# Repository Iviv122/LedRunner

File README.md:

|Index|Quantity|Part Number          |Manufacturer Part Number|Description                     |Customer Reference|Available|Backorder|Unit Price|Extended Price PLN|
|-----|--------|---------------------|------------------------|--------------------------------|------------------|---------|---------|----------|------------------|
|1    |10      |1125-1182-ND         |MT1403-RG-A             |LED RED CLEAR 3MM ROUND T/H     |                  |10       |0        |0,62700   |6,27 zł           |
|2    |1       |296-2037-5-ND        |CD4017BE                |IC DECADE COUNTER 10BIT 16DIP   |                  |1        |0        |4,66000   |4,66 zł           |
|3    |1       |399-6596-ND          |ESK105M050AC3AA         |CAP ALUM 1UF 20% 50V RADIAL TH  |                  |1        |0        |0,55000   |0,55 zł           |
|4    |1       |399-C318C104Z5U5TA-ND|C318C104Z5U5TA          |CAP CER 0.1UF 50V Z5U RADIAL    |                  |1        |0        |0,99000   |0,99 zł           |
|5    |1       |296-NE555P-ND        |NE555P                  |IC OSC SINGLE TIMER 100KHZ 8-DIP|                  |1        |0        |1,87000   |1,87 zł           |
|6    |1       |T93YA-50K-ND         |T93YA503KT20            |TRIMMER 50K OHM 0.5W PC PIN TOP |                  |1        |0        |6,79000   |6,79 zł           |
|7    |2       |CF14JT1K00CT-ND      |CF14JT1K00              |RES 1K OHM 5% 1/4W AXIAL        |                  |2        |0        |0,37000   |0,74 zł           |
|8    |1       |738-RSMF1JT460RCT-ND |RSMF1JT460R             |RES 460 OHM 5% 1W AXIAL         |                  |1        |0        |0,51000   |0,51 zł           |

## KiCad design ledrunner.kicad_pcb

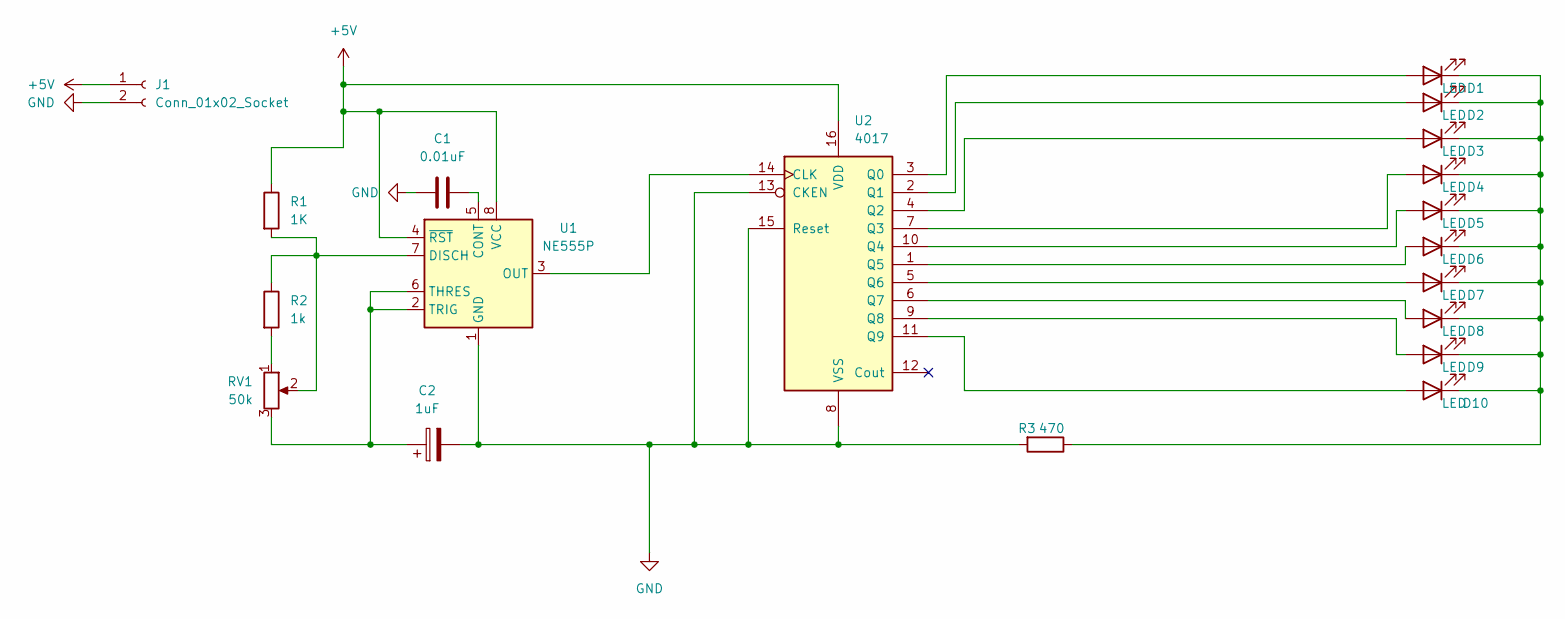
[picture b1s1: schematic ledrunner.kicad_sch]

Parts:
C1: 0.01uF; C_Disc_D7.5mm_W5.0mm_P5.00mm
C2: 1uF; CP_Radial_D5.0mm_P2.00mm
D1, D2, D3, D4, D5, D6, D7, D8, D9, D10: LED; LED_D3.0mm
J1: Conn_01x02_Socket; PinHeader_1x02_P2.54mm_Vertical
R1: 1K; R_Axial_DIN0207_L6.3mm_D2.5mm_P7.62mm_Horizontal
R2: 1k; R_Axial_DIN0207_L6.3mm_D2.5mm_P7.62mm_Horizontal
R3: 470; R_Axial_DIN0207_L6.3mm_D2.5mm_P7.62mm_Horizontal
RV1: 50k; Potentiometer_Vishay_T93YA_Vertical
U1: NE555P; DIP-8_W7.62mm
U2: 4017; N16

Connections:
+5V: J1.1, R1.1, U1.4 (~RST), U1.8 (VCC), U2.16 (VDD)
GND: C1.1, C2.2, J1.2, R3.2, U1.1 (GND), U2.8 (VSS), U2.13 (CKEN), U2.15 (Reset)
unnamed: D1.2 (A), U2.3 (Q0)
unnamed: D1.1 (K), D2.1 (K), D3.1 (K), D4.1 (K), D5.1 (K), D6.1 (K), D7.1 (K), D8.1 (K), D9.1 (K), D10.1 (K), R3.1
unnamed: D2.2 (A), U2.2 (Q1)
unnamed: D3.2 (A), U2.4 (Q2)
unnamed: D4.2 (A), U2.7 (Q3)
unnamed: D5.2 (A), U2.10 (Q4)
unnamed: D6.2 (A), U2.1 (Q5)
unnamed: D7.2 (A), U2.5 (Q6)
unnamed: D8.2 (A), U2.6 (Q7)
unnamed: D9.2 (A), U2.9 (Q8)
unnamed: D10.2 (A), U2.11 (Q9)
unnamed: R2.2, RV1.1
unnamed: C1.2, U1.5 (CONT)
unnamed: R1.2, R2.1, RV1.2, U1.7 (DISCH)
unnamed: U1.3 (OUT), U2.14 (CLK)
unnamed: C2.1, RV1.3, U1.2 (TRIG), U1.6 (THRES)

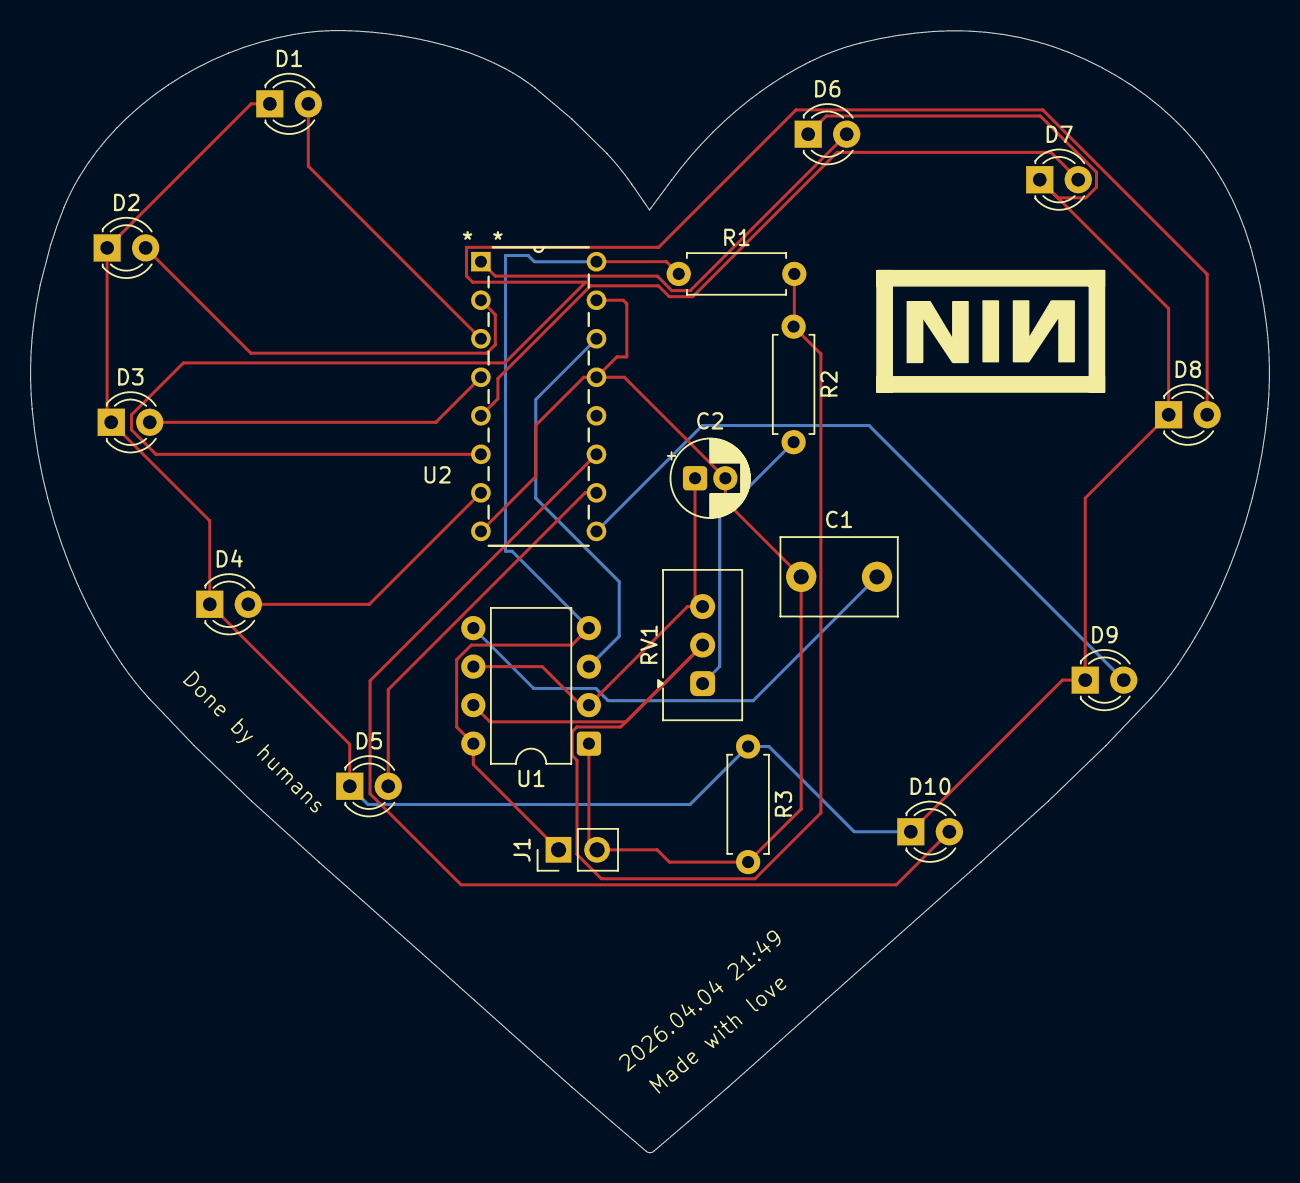
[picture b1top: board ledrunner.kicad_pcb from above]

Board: 2 copper layers, 81.7 x 74.0 mm, 19 parts (0 on the bottom side), 18 nets.

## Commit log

2026-04-04 bases
2026-04-05 modelsc
2026-04-05 gerber
